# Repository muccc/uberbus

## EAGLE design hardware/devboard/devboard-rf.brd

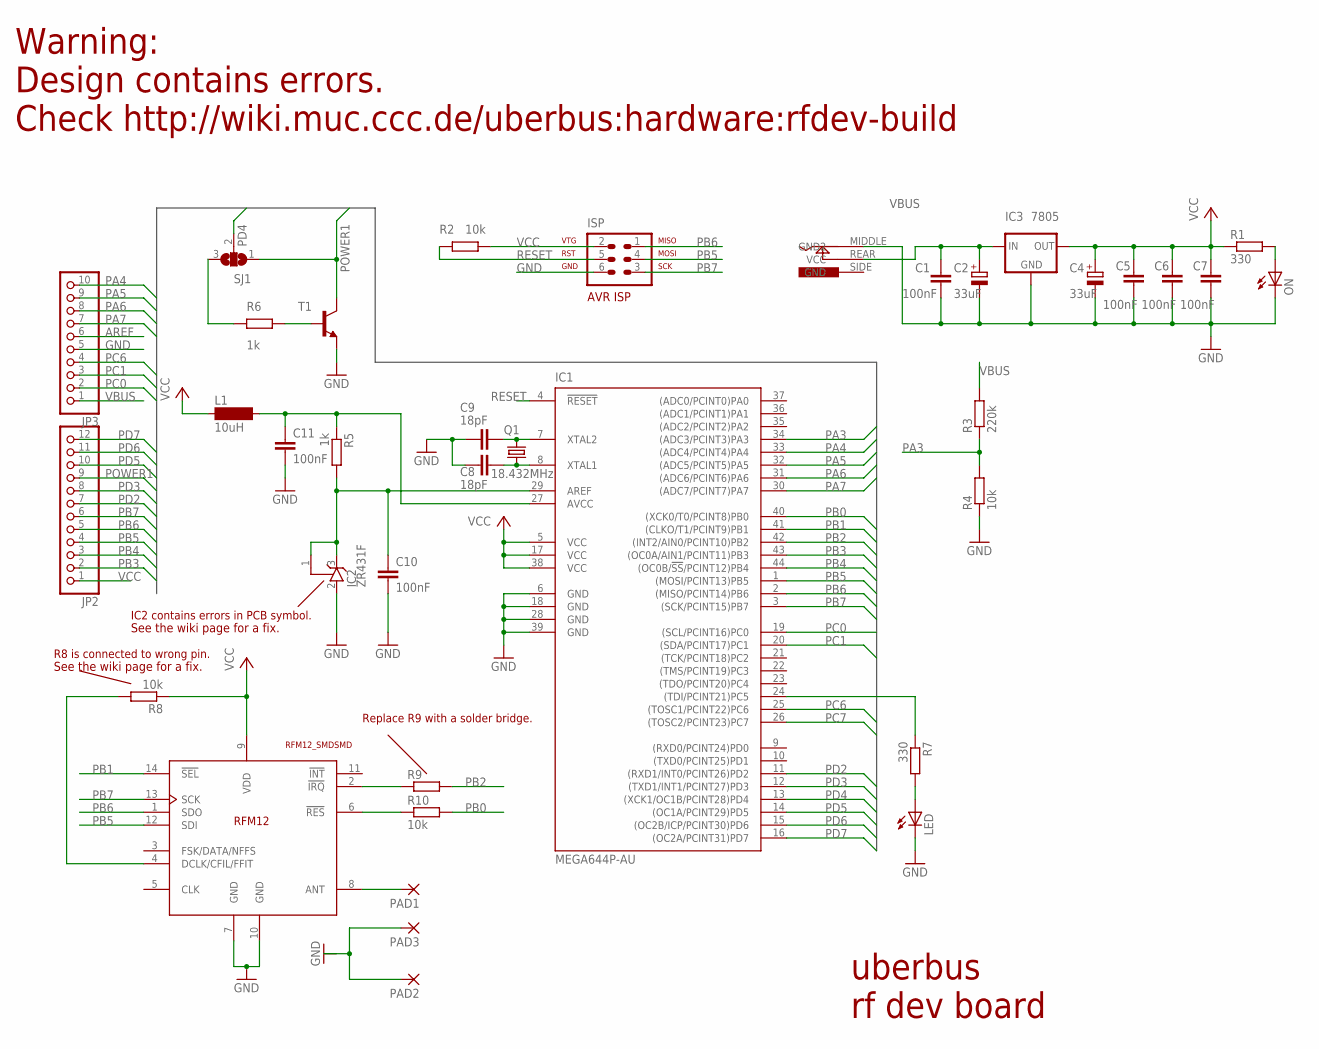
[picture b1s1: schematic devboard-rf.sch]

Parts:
C1, C5, C6, C7, C10, C11: 100nF; C0805K
C2, C4: 33uF; E2,5-5
C8, C9: 18pF; C0805K
IC1: MEGA644P-AU; TQFP44
IC2: ZR431F; SOT32
IC3: 7805; 78XXS
ISP: AVR-ISP-6
JP2: PINHD-1X12; 1X12
JP3: PINHD-1X10; 1X10
L1: 10uH; SM-1206
LED: LEDCHIPLED_0805; CHIPLED_0805
ON: LEDCHIPLED_0805; CHIPLED_0805
PAD1, PAD2, PAD3: SMD2; SMD1,27-2,54
Q1: 18.432MHz; HC49UP
R1, R7: 330; R0805
R2, R4, R8, R10: 10k; R0805
R3: 220k; R0805
R5, R6: 1k; R0805
R9: 0; R0805
SJ1: SJ2W; SJ_2
T1: MMBT2222ALT1-NPN-SOT23-BEC; SOT23-BEC
U$1: RFM12_SMDSMD; RFM12
U$2: JACK-2.1MM

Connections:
AREF: C10.1, IC1.29 (AREF), IC2.1 (R), IC2.3 (C), JP3.6, R5.2
AVCC: C11.1, IC1.27 (AVCC), L1.2, R5.1
GND: C1.1, C2.-, C4.-, C5.1, C6.1, C7.1, C8.2, C9.2, C10.2, C11.2, IC1.6 (GND), IC1.18 (GND), IC1.28 (GND), IC1.39 (GND), IC2.2 (A), IC3.GND, ISP.6, JP3.5, LED.C, ON.C, R4.1, T1.E, U$1.7 (GND), U$1.10 (GND), U$2.MIDDLE (GND2)
unnamed: C8.1, IC1.8 (XTAL1), Q1.1
unnamed: C9.1, IC1.7 (XTAL2), Q1.2
unnamed: LED.A, R7.2
unnamed: PAD2.1, PAD3.1
unnamed: R10.1, U$1.6 (!RES)
unnamed: R9.1, U$1.2 (!IRQ)
unnamed: R6.2, SJ1.3
unnamed: PAD1.1, U$1.8 (ANT)
unnamed: R8.2, U$1.4 (DCLK/CFIL/FFIT)
unnamed: R6.1, T1.B
unnamed: ON.A, R1.2
unnamed: IC1.24 ((TDI/PCINT21)PC5), R7.1
PA3: IC1.34 ((ADC3/PCINT3)PA3), R3.1, R4.2
PA4: IC1.33 ((ADC4/PCINT4)PA4), JP3.10
PA5: IC1.32 ((ADC5/PCINT5)PA5), JP3.9
PA6: IC1.31 ((ADC6/PCINT6)PA6), JP3.8
PA7: IC1.30 ((ADC7/PCINT7)PA7), JP3.7
PB0: IC1.40 ((XCK0/T0/PCINT8)PB0), R10.2
PB1: IC1.41 ((CLKO/T1/PCINT9)PB1), U$1.14 (!SEL)
PB2: IC1.42 ((INT2/AIN0/PCINT10)PB2), R9.2
PB3: IC1.43 ((OC0A/AIN1/PCINT11)PB3), JP2.2
PB4: IC1.44 ((OC0B/!SS!/PCINT12)PB4), JP2.3
PB5: IC1.1 ((MOSI/PCINT13)PB5), ISP.4, JP2.4, U$1.12 (SDI)
PB6: IC1.2 ((MISO/PCINT14)PB6), ISP.1, JP2.5, U$1.1 (SDO)
PB7: IC1.3 ((SCK/PCINT15)PB7), ISP.3, JP2.6, U$1.13 (SCK)
PC0: IC1.19 ((SCL/PCINT16)PC0), JP3.2
PC1: IC1.20 ((SDA/PCINT17)PC1), JP3.3
PC6: IC1.25 ((TOSC1/PCINT22)PC6), JP3.4
PC7: IC1.26 ((TOSC2/PCINT23)PC7)
PD2: IC1.11 ((RXD1/INT0/PCINT26)PD2), JP2.7
PD3: IC1.12 ((TXD1/INT1/PCINT27)PD3), JP2.8
PD4: IC1.13 ((XCK1/OC1B/PCINT28)PD4), SJ1.2
PD5: IC1.14 ((OC1A/PCINT29)PD5), JP2.10
PD6: IC1.15 ((OC2B/ICP/PCINT30)PD6), JP2.11
PD7: IC1.16 ((OC2A/PCINT31)PD7), JP2.12
POWER1: JP2.9, SJ1.1, T1.C
RESET: IC1.4 (!RESET), ISP.5, R2.1
VBUS: C1.2, C2.+, IC3.IN, JP3.1, R3.2, U$2.REAR (VCC)
VCC: C4.+, C5.2, C6.2, C7.2, IC1.5 (VCC), IC1.17 (VCC), IC1.38 (VCC), IC3.OUT, ISP.2, JP2.1, L1.1, R1.1, R2.2, R8.1, U$1.9 (VDD)

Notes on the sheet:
Warning:
Design contains errors.
Check http://wiki.muc.ccc.de/uberbus:hardware:rfdev-build
IC2 contains errors in PCB symbol.
Replace R9 with a solder bridge.
R8 is connected to wrong pin.
uberbus
rf dev board
See the wiki page for a fix.

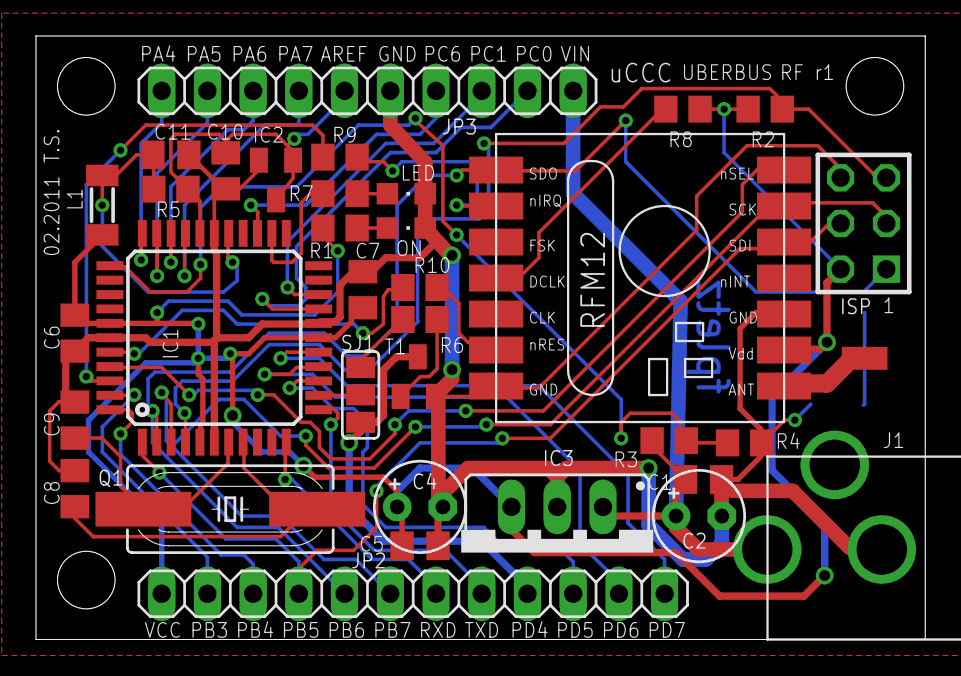
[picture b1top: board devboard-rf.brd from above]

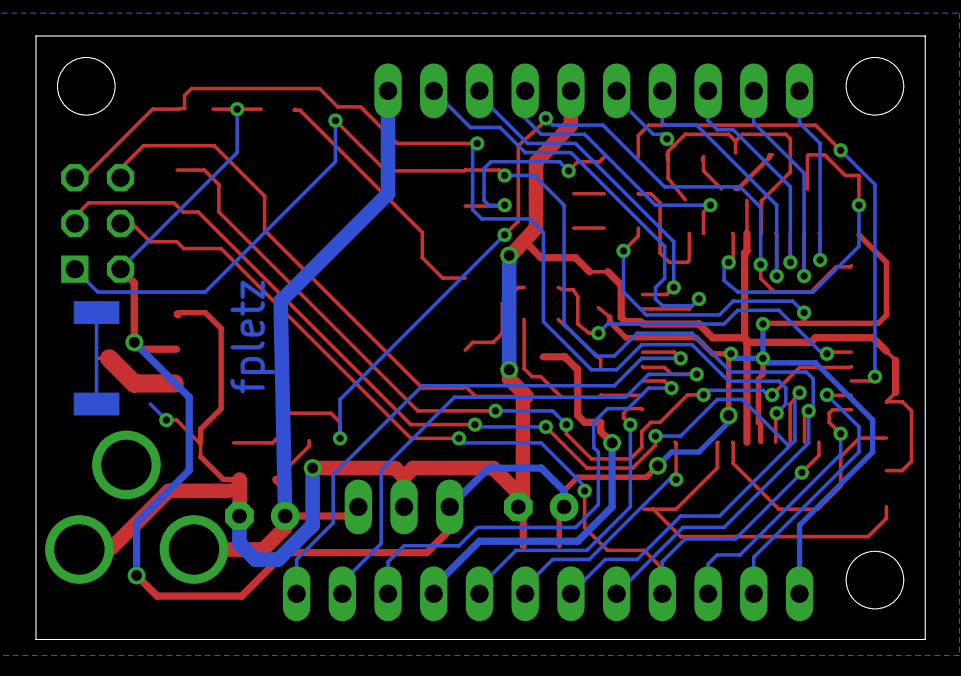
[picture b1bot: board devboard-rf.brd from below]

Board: 2 copper layers, 49.4 x 33.5 mm, 37 parts (2 on the bottom side), 41 nets.

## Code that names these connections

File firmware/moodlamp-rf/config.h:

/* vim:fdm=marker ts=4 et ai
 * {{{
 *         fnordlicht firmware next generation
 *
 *    for additional information please
 *    see http://koeln.ccc.de/prozesse/running/fnordlicht
 *
 * (c) by Alexander Neumann <alexander@bumpern.de>
 *     Lars Noschinski <lars@public.noschinski.de>
 *
 * This program is free software; you can redistribute it and/or modify
 * it under the terms of the GNU General Public License version 2 as
 * published by the Free Software Foundation.
 *
 * This program is distributed in the hope that it will be useful,
 * but WITHOUT ANY WARRANTY; without even the implied warranty of
 * MERCHANTABILITY or FITNESS FOR A PARTICULAR PURPOSE.  See the
 * GNU General Public License for more details.
 *
 * You should have received a copy of the GNU General Public License
 * along with this program; if not, write to the Free Software
 * Foundation, Inc., 675 Mass Ave, Cambridge, MA 02139, USA.
 *
 * For more information on the GPL, please go to:
 * http://www.gnu.org/copyleft/gpl.html
 }}} */

#ifndef _FNORDLICHT_CONFIG_H
#define _FNORDLICHT_CONFIG_H

#define BOARD_RF_0_2    2       //current rf board

#ifndef BOARD
#define BOARD   BOARD_RF_0_2
#endif

#ifndef LED_PORT
#define LED_PORT PORTA
#endif

#ifndef LED_PORT_DDR
#define LED_PORT_DDR DDRA
#endif

#ifndef LED_PORT_INVERT
#define LED_PORT_INVERT 0
#endif

#define FAST_PWM

/* color <-> channel assignment */
#define CHANNEL_RED     0
#define CHANNEL_GREEN   1
#define CHANNEL_BLUE    2

#define RC5_DECODER 1
#define SCRIPT_SPEED_CONTROL 1
#define STATIC_SCRIPTS 1

#define CONFIG1_PIN     PB0
#define CONFIG1_PORT     B

#define JUMPER1C1_PIN     PC3
#define JUMPER1C1_PORT    C

#define JUMPER1C2_PIN     PC3
#define JUMPER1C2_PORT    C

#define LED3_PIN     PA4
#define LED3_PORT    A

#define LED2_PIN     PA5
#define LED2_PORT    A

#define LED1_PIN     PA7
#define LED1_PORT    A

#define xRC5C2_PORT     PORTB
#define	xRC5C2_IN       PINB
#define	xRC5C2          PB1			// IR input low active

#define xRC5C1_PORT     PORTD
#define	xRC5C1_IN       PIND
#define	xRC5C1          PD6			// IR input low active

#define ADC_MINBATIDLE  530         //4v

/* debug defines */
#ifndef DEBUG
#define DEBUG 0
#endif

/* include the script intpreter per default */
#ifndef STATIC_SCRIPTS
#define STATIC_SCRIPTS 1
#endif

/* disable rc5-decoder per default */
#ifndef RC5_DECODER
#define RC5_DECODER 1
#endif

/* disable scripts speed control per default */
#ifndef SCRIPT_SPEED_CONTROL
#define SCRIPT_SPEED_CONTROL 1
#endif

#ifndef PWM_USESCALE
#define PWM_USESCALE
#endif

#include <avr/version.h>

/* check for avr-libc version */
#if __AVR_LIBC_VERSION__ < 10604UL
#error newer libc version (>= 1.6.4) needed!
#endif

/* check if cpu speed is defined */
#ifndef F_CPU
#error please define F_CPU!
#endif

/* check if this cpu is supported */
#if !(defined(__AVR_ATmega8__) || defined(__AVR_ATmega88__) || defined(__AVR_ATmega168__) || defined(__AVR_ATmega16__) || defined(__AVR_ATmega324P__)  || defined(__AVR_ATmega644P__) || defined(__AVR_ATmega32__))
#error "this cpu isn't supported yet!"
#endif

/* cpu specific configuration registers */
#if defined(__AVR_ATmega8__)
/* {{{ */
#define _ATMEGA8

#define _TIMSK_TIMER1 TIMSK
#define _UCSRB_UART0 UCSRB
#define _UDRIE_UART0 UDRIE
#define _TXEN_UART0 TXEN
#define _RXEN_UART0 RXEN
#define _RXCIE_UART0 RXCIE
#define _UBRRH_UART0 UBRRH
#define _UBRRL_UART0 UBRRL
#define _UCSRC_UART0 UCSRC
#define _UCSZ0_UART0 UCSZ0
#define _UCSZ1_UART0 UCSZ1
#define _SIG_UART_RECV_UART0 SIG_UART_RECV
#define _SIG_UART_DATA_UART0 SIG_UART_DATA
#define _UDR_UART0 UDR
#define UCSR0A UCSRA
#define UCSR0C UCSRC
#define MPCM0 MPCM
#define UCSZ00 UCSZ0
#define UCSZ01 UCSZ1
#define UCSZ02 UCSZ2
#define UBRR0H UBRRH
#define UBRR0L UBRRL
#define UCSR0B UCSRB
#define RXEN0 RXEN
#define TXEN0 TXEN
#define RXC0 RXC
#define RXB80 RXB8
#define UDR0 UDR

/* }}} */
#elif defined(__AVR_ATmega16__) || defined(__AVR_ATmega32__)
/* {{{ */
#define _ATMEGA16

#define _EICRA MCUCR
#define _EIMSK GICR
#define _TIMSK_TIMER1 TIMSK
#define _UCSRB_UART0 UCSRB
#define _UDRIE_UART0 UDRIE
#define _TXEN_UART0 TXEN
#define _RXEN_UART0 RXEN
#define _RXCIE_UART0 RXCIE
#define _UBRRH_UART0 UBRRH
#define _UBRRL_UART0 UBRRL
#define _UCSRC_UART0 UCSRC
#define _UCSZ0_UART0 UCSZ0
#define _UCSZ1_UART0 UCSZ1
#define _SIG_UART_RECV_UART0 SIG_UART_RECV
#define _SIG_UART_DATA_UART0 SIG_UART_DATA
#define _UDR_UART0 UDR
#define UCSR0A UCSRA
#define UCSR0C UCSRC
#define MPCM0 MPCM
#define UCSZ00 UCSZ0
#define UCSZ01 UCSZ1
#define UCSZ02 UCSZ2
#define UBRR0H UBRRH
#define UBRR0L UBRRL
#define UCSR0B UCSRB
#define RXEN0 RXEN
#define TXEN0 TXEN
#define RXC0 RXC
#define RXB80 RXB8
#define UDR0 UDR

/* }}} */

#elif defined(__AVR_ATmega88__) || defined(__AVR_ATmega168__)|| defined(__AVR_ATmega324P__) || defined(__AVR_ATmega644P__)
/* {{{ */
#define _ATMEGA88
#define _EICRA EICRA
#define _EIMSK EIMSK
#define _TIMSK_TIMER1 TIMSK1
#define _UCSRB_UART0 UCSR0B
#define _UDRIE_UART0 UDRIE0
#define _TXEN_UART0 TXEN0
#define _RXEN_UART0 RXEN0
#define _RXCIE_UART0 RXCIE0
#define _UBRRH_UART0 UBRR0H
#define _UBRRL_UART0 UBRR0L
#define _UCSRC_UART0 UCSR0C
#define _UCSZ0_UART0 UCSZ00
#define _UCSZ1_UART0 UCSZ01
#define _SIG_UART_RECV_UART0 USART0_RX_vect
#define _SIG_UART_DATA_UART0 USART0_UDRE_vect
#define _UDR_UART0 UDR0
/* }}} */
#endif


#endif /* _FNORDLICHT_CONFIG_H */

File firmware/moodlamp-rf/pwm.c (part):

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
    /* load initial delay, trigger an overflow */
    OCR1B = 65000;
    //DDRD |= (1<<PD6)|(1<<PD5)|(1<<PD4)|(1<<PD3);
}

/* }}} */
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/*{{{*/ {
    uint8_t i;

    //PORTC ^= (1<<PC1);
    /* iterate over the channels */
    for (i=0; i<PWM_CHANNELS; i++) {
        uint8_t old_brightness;
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
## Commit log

2011-07-03 updated alarm scripts
2011-07-03 added digitalio to pythonlib
2011-09-18 simplified the ubcolorgui
2011-09-25 moved to glib mainloop added avahi discover
2011-09-25 lcdcontroller: read groups from mdns
2011-09-25 ircbot: added !alarm
2011-09-25 hsvcontroller: typo
2011-09-25 lcdcontroller: repeat timer
2011-10-04 removed libutil dependency
2011-10-19 got rid of avahi-client(and dbus for that matter!)
2011-10-20 removed debug code
2011-11-20 ubvahid: added _simple_ json to avahi bridge
2011-11-21 ubavahid: added working openwrt makefile
2011-11-22 ubavahid: read interface and group from cl
2011-11-22 ubavahid: added openwrt init script
2011-11-23 ubavahid now has its own repository
2011-11-23 removed old code
2011-11-29 added multicastforwarding daemon
2012-02-13 ubnode: removed dead code
2012-02-13 hid: limited lcd size to 16 chars
2012-02-13 added get command to digitaloutput
2012-02-13 lcdcontroller example: lots of features...
2012-02-13 merged changes
2012-02-13 updated resolver to report the port of a service
2012-02-16 restored broken digitaloutput
2012-02-16 pythonlib: digitaloutput: fixed missing import
2012-02-19 ubnode: more error handling
2012-04-01 devboard-rf: cleaned up schematic
2014-05-30 fix(libc): use new interrupt names
